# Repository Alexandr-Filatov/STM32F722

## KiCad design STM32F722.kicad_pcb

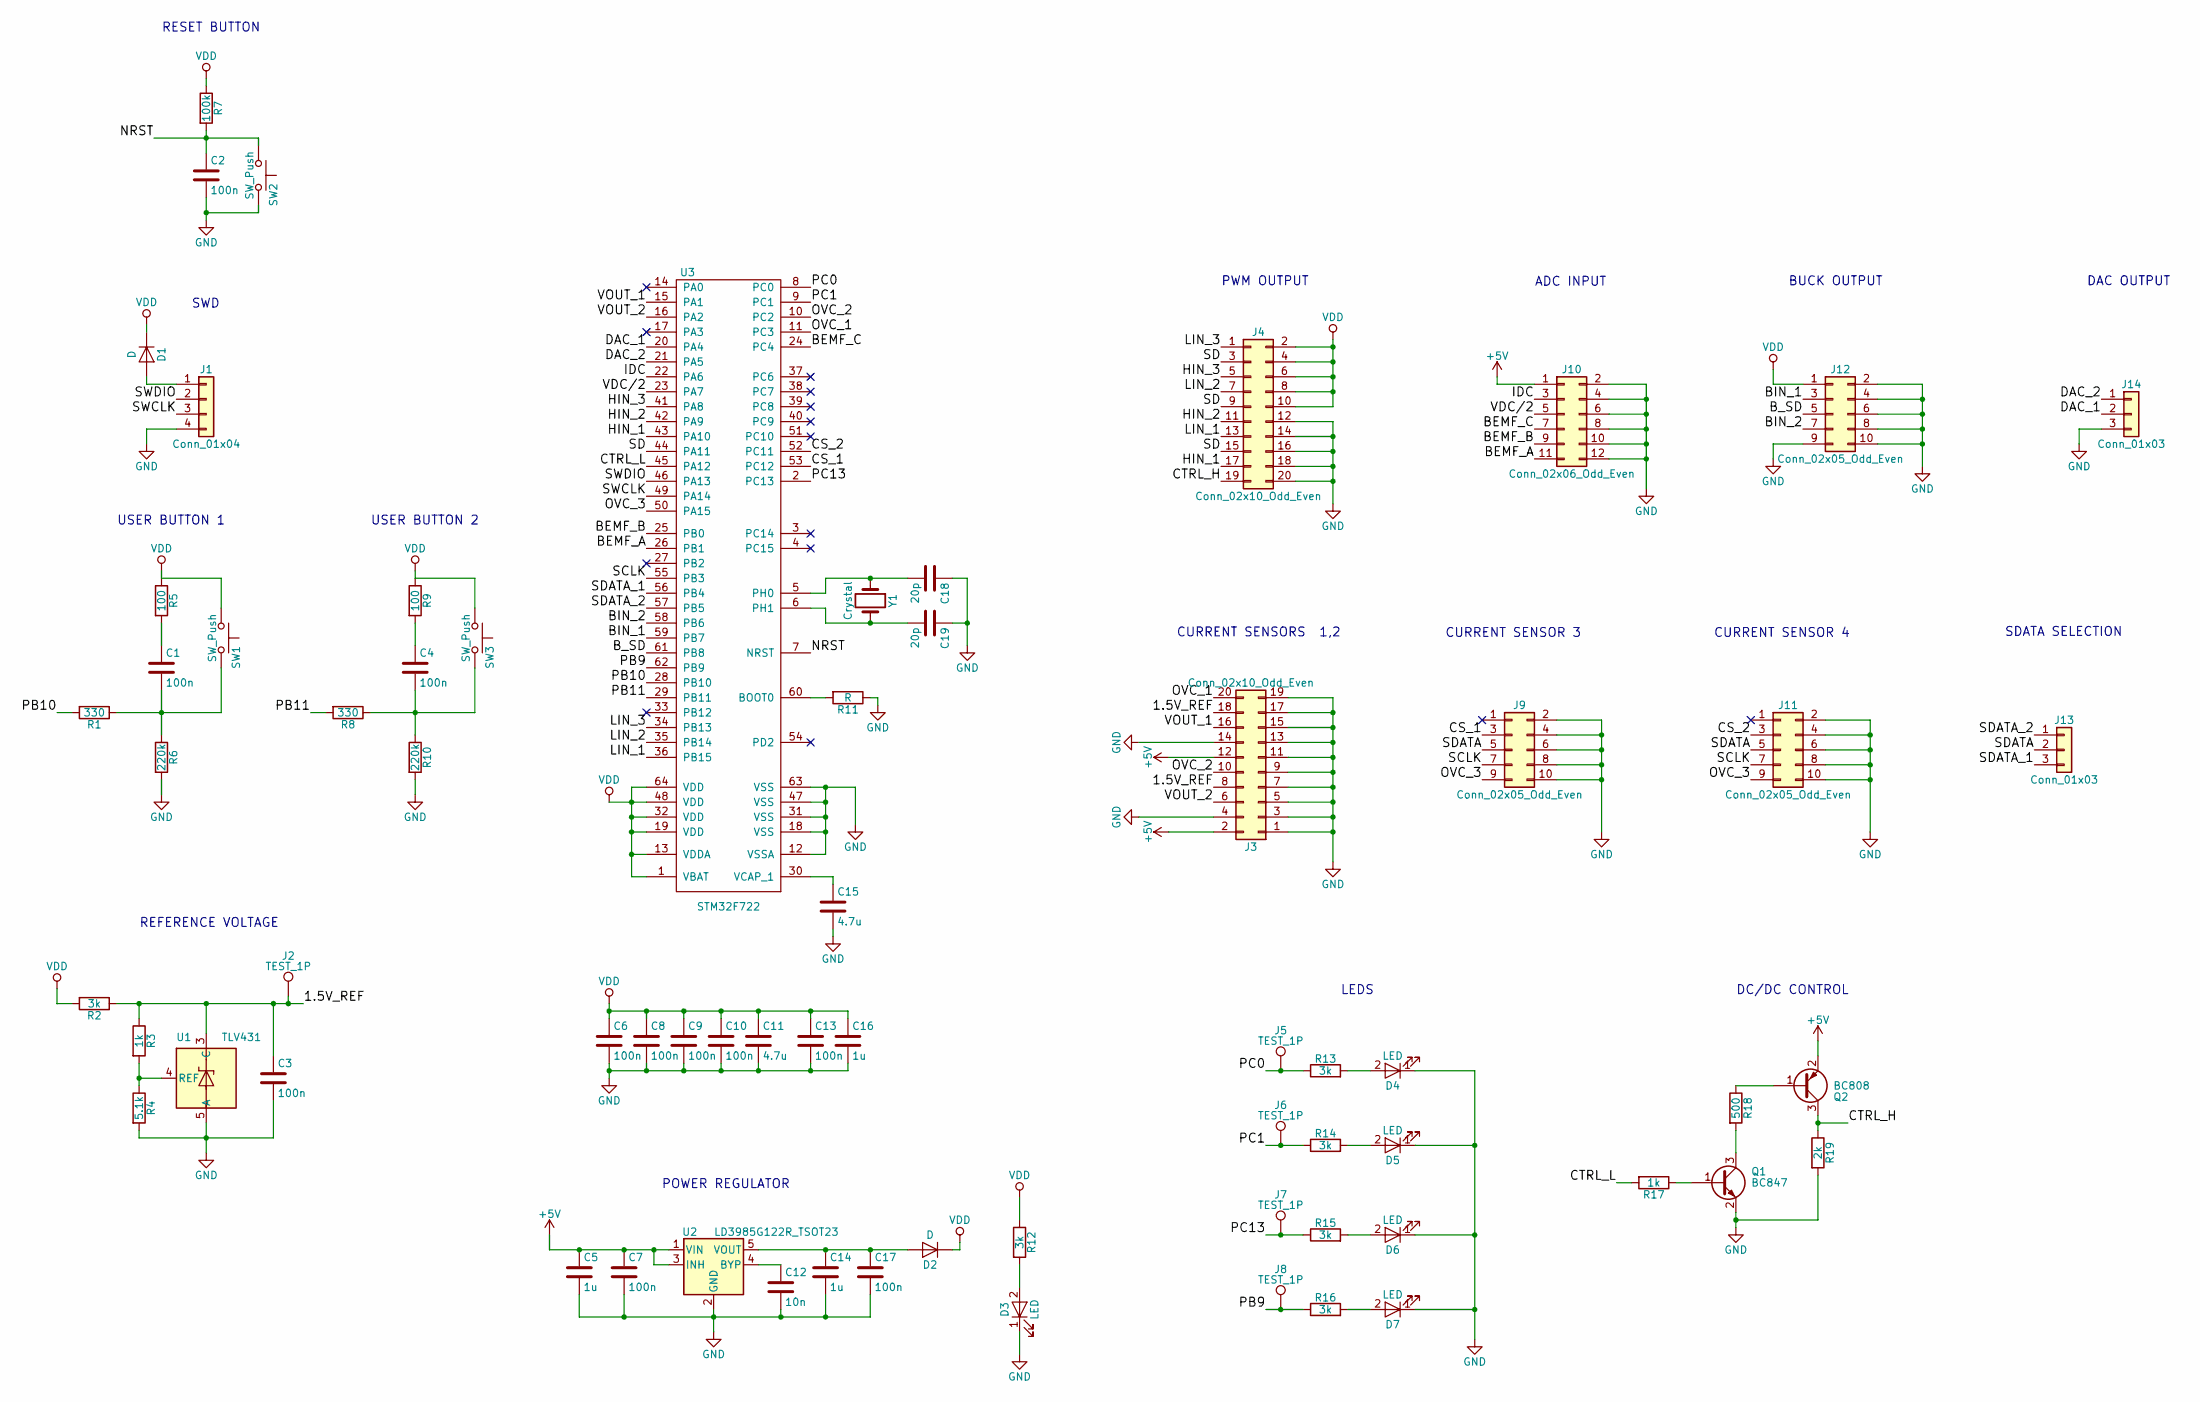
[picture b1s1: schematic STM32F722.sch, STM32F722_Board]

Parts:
C1, C2, C3, C4, C6, C7, C8, C9, C10, C13, C17: 100n; C_0805_HandSoldering
C5, C14, C16: 1u; C_0805_HandSoldering
C11, C15: 4.7u; C_0805_HandSoldering
C12: 10n; C_0805_HandSoldering
C18, C19: 20p; C_0805_HandSoldering
D1, D2: D; D_SOD-323_HandSoldering
D3, D4, D5, D6, D7: LED; LED_0805_HandSoldering
J1: Conn_01x04
J2, J5, J6, J7, J8: TEST_1P; TestPin
J3: Conn_02x10_Odd_Even; IDC-20MS
J4: Conn_02x10_Odd_Even; Conn_02x10
J9, J11, J12: Conn_02x05_Odd_Even; IDC-10MS
J10: Conn_02x06_Odd_Even; Conn_02x06
J13, J14: Conn_01x03
Q1: BC847; SOT-23
Q2: BC808; SOT-23
R1, R8: 330; R_0805_HandSoldering
R2, R12, R13, R14, R15, R16: 3k; R_0805_HandSoldering
R3, R17: 1k; R_0805_HandSoldering
R4: 5.1k; R_0805_HandSoldering
R5, R9: 100; R_0805_HandSoldering
R6, R10: 220k; R_0805_HandSoldering
R7: 100k; R_0805_HandSoldering
R11: R; R_0805_HandSoldering
R18: 500; R_0805_HandSoldering
R19: 2k; R_0805_HandSoldering
SW1, SW2, SW3: SW_Push; SW_PUSH_6mm
U1: TLV431; SOT-23-5
U2: LD3985G122R_TSOT23; TSOT-23-5
U3: STM32F722; LQFP-64_10x10mm_Pitch0.5mm
Y1: Crystal; Oscillator_SMD_Fordahl_DFAS15-4pin_5.0x3.2mm_HandSoldering

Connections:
+5V: C5.1, C7.1, J3.2, J3.12, J10.1, Q2.2 (E), U2.1 (VIN), U2.3 (INH)
/1.5V_REF: C3.1, J2.1, J3.8, J3.18, R2.1, R3.1, U1.3 (C)
/BEMF_A: J10.11, U3.26 (PB1)
/BEMF_B: J10.9, U3.25 (PB0)
/BEMF_C: J10.7, U3.24 (PC4)
/BIN_1: J12.3, U3.59 (PB7)
/BIN_2: J12.7, U3.58 (PB6)
/B_SD: J12.5, U3.61 (PB8)
/CS_1: J9.3, U3.53 (PC12)
/CS_2: J11.3, U3.52 (PC11)
/CTRL_H: J4.19, Q2.3 (C), R19.1
/CTRL_L: R17.2, U3.45 (PA12)
/DAC_1: J14.2, U3.20 (PA4)
/DAC_2: J14.1, U3.21 (PA5)
/HIN_1: J4.17, U3.43 (PA10)
/HIN_2: J4.11, U3.42 (PA9)
/HIN_3: J4.5, U3.41 (PA8)
/IDC: J10.3, U3.22 (PA6)
/LIN_1: J4.13, U3.36 (PB15)
/LIN_2: J4.7, U3.35 (PB14)
/LIN_3: J4.1, U3.34 (PB13)
/NRST: C2.1, R7.2, SW2.1, U3.7 (NRST)
/OVC_1: J3.20, U3.11 (PC3)
/OVC_2: J3.10, U3.10 (PC2)
/OVC_3: J9.9, J11.9, U3.50 (PA15)
/PB9: J8.1, R16.1, U3.62 (PB9)
/PB10: R1.2, U3.28 (PB10)
/PB11: R8.2, U3.29 (PB11)
/PC0: J5.1, R13.1, U3.8 (PC0)
/PC1: J6.1, R14.1, U3.9 (PC1)
/PC13: J7.1, R15.1, U3.2 (PC13)
/SCLK: J9.7, J11.7, U3.55 (PB3)
/SD: J4.3, J4.9, J4.15, U3.44 (PA11)
/SDATA: J9.5, J11.5, J13.2
/SDATA_1: J13.3, U3.56 (PB4)
/SDATA_2: J13.1, U3.57 (PB5)
/SWCLK: J1.3, U3.49 (PA14)
/SWDIO: J1.2, U3.46 (PA13)
/VDC/2: J10.5, U3.23 (PA7)
/VOUT_1: J3.16, U3.15 (PA1)
/VOUT_2: J3.6, U3.16 (PA2)
GND: C2.2, C3.2, C5.2, C6.2, C7.2, C8.2, C9.2, C10.2, C11.2, C12.2, C13.2, C14.2, C15.2, C16.2, C17.2, C18.1, C19.1, D3.1 (K), D4.1 (K), D5.1 (K), D6.1 (K), D7.1 (K), J1.4, J3.1, J3.3, J3.4, J3.5, J3.7, J3.9, J3.11, J3.13, J3.14, J3.15, J3.17, J3.19, J4.12, J4.14, J4.16, J4.18, J4.20, J9.2, J9.4, J9.6, J9.8, J9.10, J10.2, J10.4, J10.6, J10.8, J10.10, J10.12, J11.2, J11.4, J11.6, J11.8, J11.10, J12.2, J12.4, J12.6, J12.8, J12.9, J12.10, J14.3, Q1.2 (E), R4.2, R6.2, R10.2, R11.1, R19.2, SW2.2, U1.5 (A), U2.2 (GND), U3.12 (VSSA), U3.18 (VSS), U3.31 (VSS), U3.47 (VSS), U3.63 (VSS)
unnamed: C1.1, R5.2
unnamed: C1.2, R1.1, R6.1, SW1.2
unnamed: C4.1, R9.2
unnamed: C4.2, R8.1, R10.1, SW3.2
unnamed: C12.1, U2.4 (BYP)
unnamed: C14.1, C17.1, D2.2 (A), U2.5 (VOUT)
unnamed: C15.1, U3.30 (VCAP_1)
unnamed: C18.2, U3.5 (PH0), Y1.1
unnamed: C19.2, U3.6 (PH1), Y1.2
unnamed: D1.2 (A), J1.1
unnamed: D3.2 (A), R12.2
unnamed: D4.2 (A), R13.2
unnamed: D5.2 (A), R14.2
unnamed: D6.2 (A), R15.2
unnamed: D7.2 (A), R16.2
unnamed: Q1.1 (B), R17.1
unnamed: Q1.3 (C), R18.2
unnamed: Q2.1 (B), R18.1
unnamed: R3.2, R4.1, U1.4 (REF)
unnamed: R11.2, U3.60 (BOOT0)
VDD: C6.1, C8.1, C9.1, C10.1, C11.1, C13.1, C16.1, D1.1 (K), D2.1 (K), J4.2, J4.4, J4.6, J4.8, J4.10, J12.1, R2.2, R5.1, R7.1, R9.1, R12.1, SW1.1, SW3.1, U3.1 (VBAT), U3.13 (VDDA), U3.19 (VDD), U3.32 (VDD), U3.48 (VDD), U3.64 (VDD)

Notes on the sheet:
RESET BUTTON
POWER REGULATOR
SWD
USER BUTTON 2
REFERENCE VOLTAGE
PWM OUTPUT
ADC INPUT
BUCK OUTPUT
USER BUTTON 1
DAC OUTPUT
CURRENT SENSORS 1,2
CURRENT SENSOR 3
CURRENT SENSOR 4
SDATA SELECTION
LEDS
DC/DC CONTROL

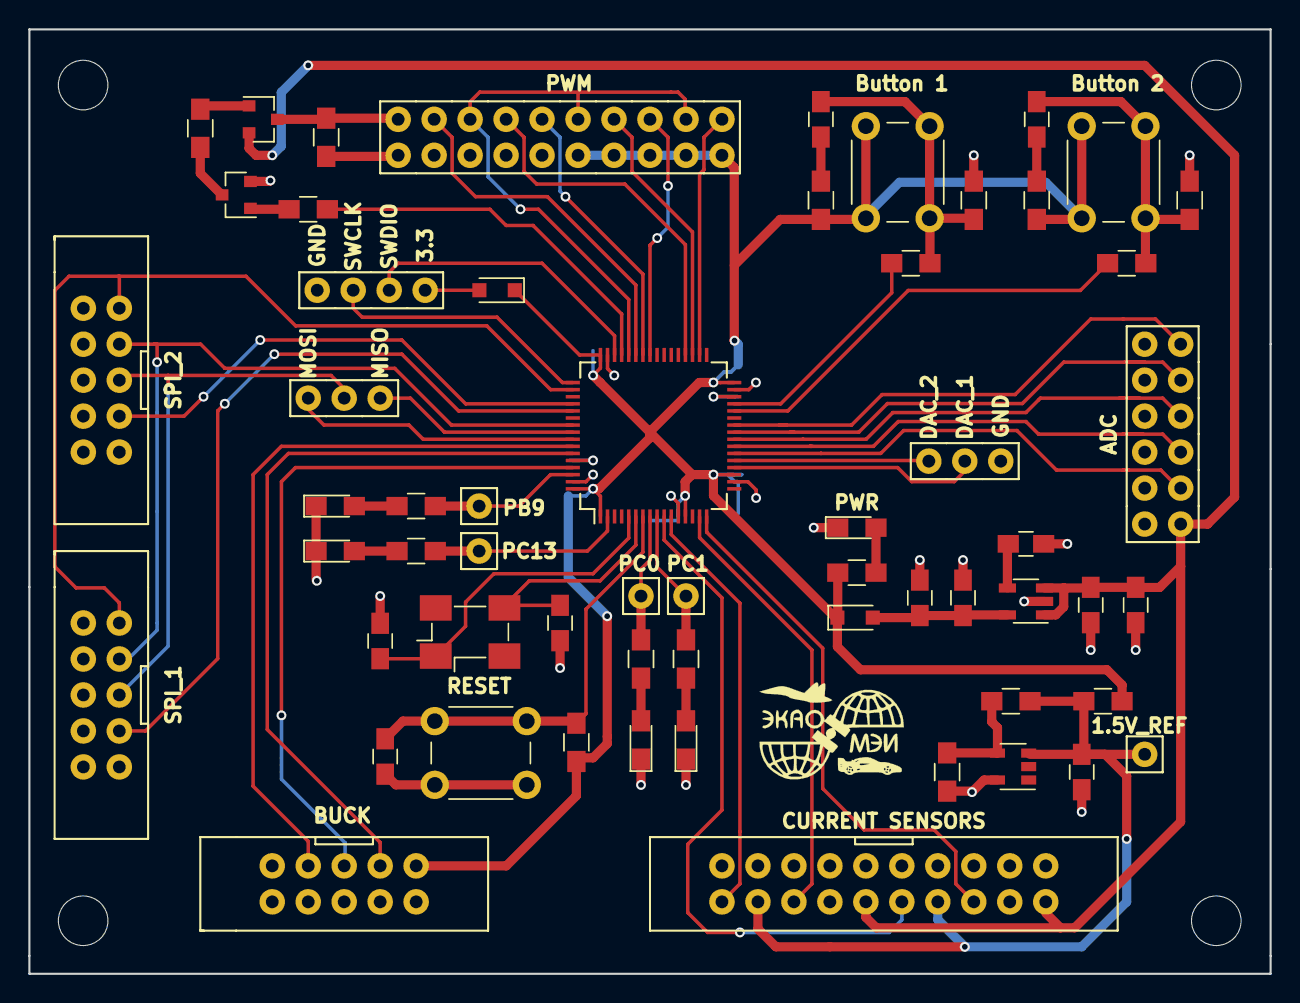
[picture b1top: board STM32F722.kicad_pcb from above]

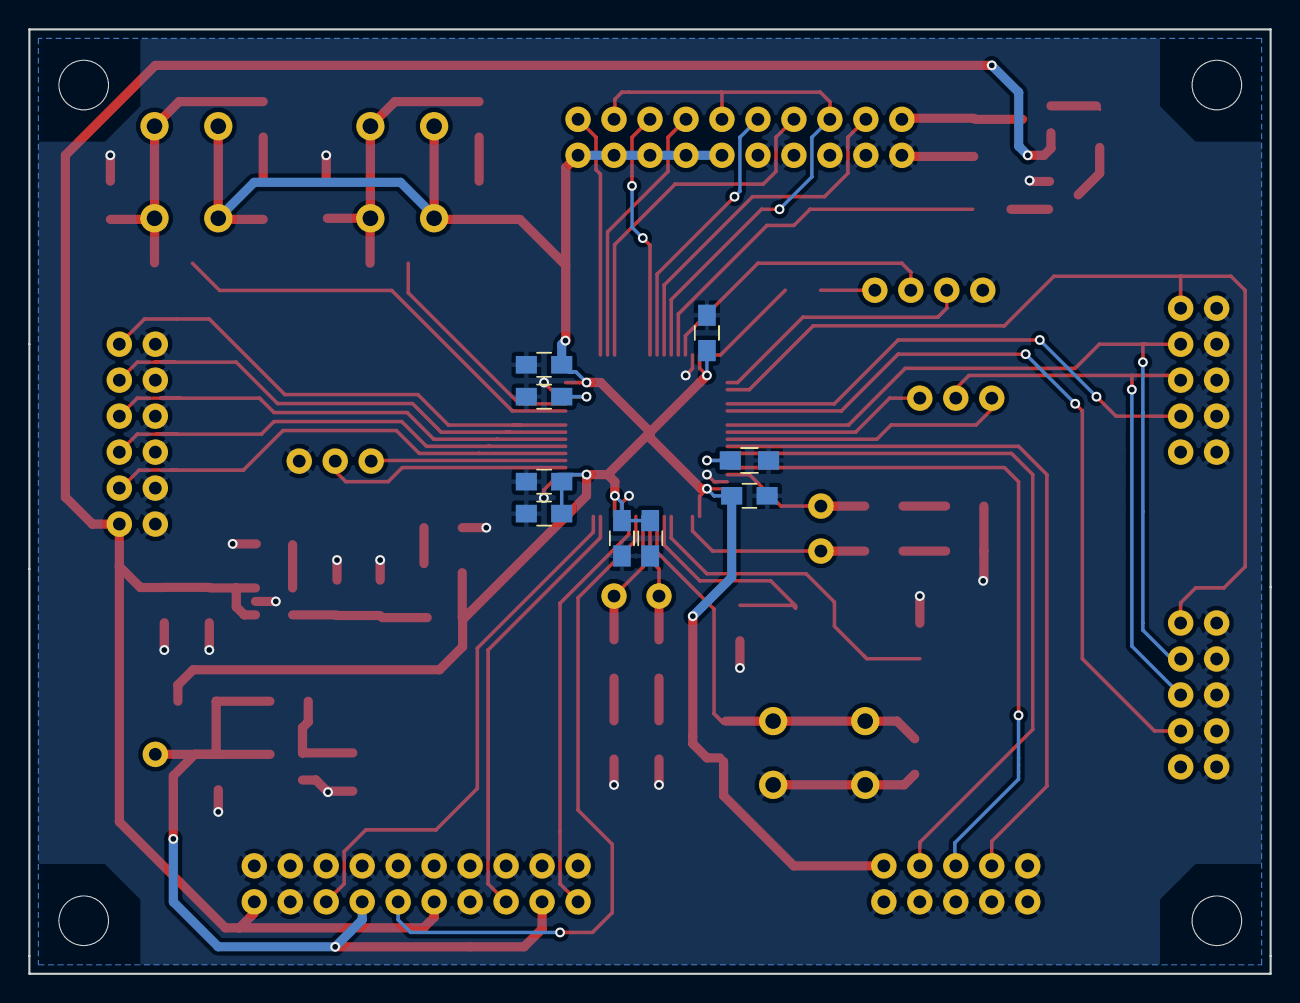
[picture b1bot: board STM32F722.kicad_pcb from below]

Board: 2 copper layers, 87.6 x 66.7 mm, 68 parts (9 on the bottom side), 63 nets.

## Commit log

2023-11-22 Нулевой коммит
